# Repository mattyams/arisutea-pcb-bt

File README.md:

# VERY MUCH ALPHA BLUETOOTH VERSION!
# THIS IS STILL A WIP! NO GUARANTEES ON ANYTHING!
# Arisutea - Arisu Bluetooth Keyboard PCB
## Disclaimer: Use these files at your own risk.
アリステア PCB designed using KiCad. The layout was originally created by FateNozomi, inspired by Lyn's EM7 and TGR Alice with some modification. The layout was then modified by CorruptedJef and robotictomato to add Bluetooth using a Holyiot 18010, USB-C, ESD and to shift/add some keys. This inspired me to modify the layout further by adding the ability to swap your switches out whenever you want and to make some keys a little more permenant. I have designed many boards in the past but never a keyboard so this is my first crack at it and I figured why not go all out? If you notice any issue please open an issue and we can discuss!

Since the layout has been modified yet again I decided to give the project a new name, Arisutea, which translates to Alistair. Obviously keeping the theme running here. 

Key modifications to the PCB:
- Bluetooth using a Holyiot 18010.
- Added in Kailh Hotswap sockets.
- Addition of full backspace position, connected to switch 59 (row 0, column 13).
  - Removed switch 63 and repositioned switch 59 to add full backspace position.
- USB-C ESD rework.
- Added LED indicators for CAPS and NUM lock as well as layer.
- Updated JSON layout file for this particular keyboard.
- Original mounting holes have been widened to allow for M2+ standoffs to pass through the PCB to the FR4 plates linked below, so if you planned on using this in a different case other than the one provided or these plates....you might have a bad time. 

# ZMK Firmware
I plan to use ZMK for this board once I get it finalized.

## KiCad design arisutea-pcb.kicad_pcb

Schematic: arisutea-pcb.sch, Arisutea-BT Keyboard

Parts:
BT1: Battery_Cell; Battery_Connector
BT2: Battery_Cell; JST_PH_S2B-PH-K_1x02_P2.00mm_Horizontal
C1: 4.7uF; C_0805_2012Metric_Pad1.18x1.45mm_HandSolder
C2, C3: 1uF; C_0805_2012Metric_Pad1.18x1.45mm_HandSolder
D1: 1N5819; D_SOD-123
F1: 500mA; Fuse_1206_3216Metric_Pad1.42x1.75mm_HandSolder
H1, H2, H3, H4, H5, H6, H7, H8: ThroughHole; Generic-Mounthole
J1: Conn_01x04; PinHeader_1x04_P2.54mm_Vertical
LED1: PWR_LED; LED_IN-S124ARUW
LED2: NUM_LOCK; LED_IN-S124ARUW
LED3: CAPS_LOCK; LED_IN-S124ARUW
LED4: FN_LED; LED_IN-S124ARUW
LED5: BAT_LED; LED_IN-S124ARUW
LOGO1, LOGO2: arisutea_logo
Q1: AO3401A; SOT-23
R1, R2: 5k1; R_0805_2012Metric_Pad1.20x1.40mm_HandSolder; LCSC C27834
R3, R4: 22; R_0805_2012Metric_Pad1.20x1.40mm_HandSolder; LCSC C17561
R5: 806K; R_0805_2012Metric_Pad1.20x1.40mm_HandSolder; LCSC C17561
R6: 2M; R_0805_2012Metric_Pad1.20x1.40mm_HandSolder; LCSC C17561
R7: 10K; R_0805_2012Metric_Pad1.20x1.40mm_HandSolder; LCSC C17561
R8: 1k; R_0805_2012Metric_Pad1.20x1.40mm_HandSolder; LCSC C17561
R9: 10K; R_0805_2012Metric_Pad1.20x1.40mm_HandSolder; LCSC C17414
R10: 1K; R_0805_2012Metric_Pad1.20x1.40mm_HandSolder; LCSC C17561
R11, R12, R13: 470; R_0805_2012Metric_Pad1.20x1.40mm_HandSolder
SW67: Switch; OS102011MA1QN1
SWR1: SW_Push; SW_SPST_TL3342; LCSC C318884
U1: nRF52840_holyiot_18010; nRF52840_holyiot_18010_HS_simple
U2: USBLC6-2SC6; SOT-23-6_Handsoldering; LCSC C7519
U3: TP4504; SOT-23-5
U4: AP2112K-3.3; SOT-23-5
USB1: HRO-TYPE-C-31-M-12-Type-C; USB_C_Receptacle_HRO_TYPE-C-31-M-12-HandSoldering

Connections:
CAPS_L: R12.2, U1.16
D+: R4.1, U1.24
D-: R3.1, U1.23
FN_L: R11.2, U1.17
GND: BT1.2, BT2.2, C1.1, C2.2, C3.2, J1.3, LED2.C, LED3.C, LED4.C, R1.1, R2.1, R6.1, R7.2, R9.2, R10.1, SWR1.1 (COL), U1.1, U1.25, U1.37, U2.2, U3.2, U4.2, USB1.1, USB1.12, USB1.13
NUM_L: R13.2, U1.15
unnamed: BT1.1, BT2.1, SW67.1 (COL)
unnamed: C3.1, D1.1, Q1.2, U4.1, U4.3
unnamed: LED1.A, R8.2
unnamed: LED1.C, U3.1
unnamed: LED2.A, R11.1
unnamed: LED3.A, R12.1
unnamed: LED4.A, R13.1
unnamed: LED5.C, R10.2
unnamed: R1.2, USB1.4
unnamed: R2.2, USB1.10
unnamed: R3.2, U2.6
unnamed: R4.2, U2.4
unnamed: R7.1, U3.5
unnamed: U2.1, USB1.5, USB1.7
unnamed: U2.3, USB1.6, USB1.8
VBUS: D1.2, F1.2, J1.4, Q1.1, R8.1, R9.1, U1.22, U3.4
VDD_nRF: C2.1, U1.14, U4.5
bat_led: LED5.A, U1.18
bat_volt: R5.1, R6.2, U1.12
col6: U1.33; also elsewhere on the board
col7: U1.34; also elsewhere on the board
col8: U1.35; also elsewhere on the board
col9: U1.36; also elsewhere on the board
col10: U1.30; also elsewhere on the board
col11: U1.29; also elsewhere on the board
col12: U1.28; also elsewhere on the board
col13: U1.27; also elsewhere on the board
col14: U1.26; also elsewhere on the board
reset: SWR1.2 (ROW), U1.21
row0: U1.11; also elsewhere on the board
row1: U1.10; also elsewhere on the board
row2: U1.5; also elsewhere on the board
row3: U1.3; also elsewhere on the board
row4: U1.4; also elsewhere on the board
swdclk: J1.2, U1.31
swdio: J1.1, U1.32
vbat: C1.2, Q1.3, R5.2, SW67.2 (ROW), U3.3
vbus_usb: F1.1, U2.5, USB1.2, USB1.11

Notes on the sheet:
USB Connection, ESD & Fuse
Battery Management
Voltage Reg & Reset Switch

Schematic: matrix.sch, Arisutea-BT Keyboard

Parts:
D2, D3, D4, D5, D6, D7, D8, D9, D10, D11, D12, D13, D14, D15, D16, D17, D18, D19, D20, D21, D22, D23, D24, D25, D26, D27, D28, D29, D30, D31, D32, D33, D34, D35, D36, D37, D38, D39, D40, D41, D42, D43, D44, D45, D46, D47, D48, D49, D50, D51, D52, D53, D54, D55, D56, D57, D58, D59, D60, D61, D62, D63, D64, D65, D66, D67: D; D_SOD-123; LCSC C81598
SW1, SW2, SW3, SW4, SW5, SW6, SW7, SW8, SW9, SW10, SW11, SW12, SW13, SW16, SW17, SW18, SW19, SW20, SW21, SW22, SW23, SW24, SW25, SW26, SW27, SW29, SW31, SW32, SW33, SW34, SW35, SW36, SW37, SW38, SW39, SW40, SW41, SW43, SW45, SW46, SW47, SW48, SW49, SW50, SW51, SW52, SW53, SW54, SW56, SW57, SW59, SW61, SW63, SW64, SW65, SW66: SW_Push; SW_Hotswap_Kailh_1.00u
SW14: SW_Push; SW_Hotswap_Kailh_2.00u
SW15, SW28, SW58: SW_Push; SW_Hotswap_Kailh_1.50u
SW30, SW55: SW_Push; SW_Hotswap_Kailh_1.75u
SW42: SW_Push; SW_Hotswap_Kailh_2.25u_RevStab
SW44: SW_Push; SW_Hotswap_Kailh_2.25u
SW60: SW_Push; SW_Hotswap_Kailh_2.00u_RevStab
SW62: SW_Push; SW_Hotswap_Kailh_2.75u_RevStab

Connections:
unnamed: D2.2 (A), SW1.2
unnamed: D3.2 (A), SW2.2
unnamed: D4.2 (A), SW3.2
unnamed: D5.2 (A), SW4.2
unnamed: D6.2 (A), SW5.2
unnamed: D7.2 (A), SW6.2
unnamed: D8.2 (A), SW7.2
unnamed: D9.2 (A), SW8.2
unnamed: D10.2 (A), SW9.2
unnamed: D11.2 (A), SW10.2
unnamed: D12.2 (A), SW11.2
unnamed: D13.2 (A), SW12.2
unnamed: D14.2 (A), SW13.2
unnamed: D15.2 (A), SW14.2
unnamed: D16.2 (A), SW15.2
unnamed: D17.2 (A), SW16.2
unnamed: D18.2 (A), SW17.2
unnamed: D19.2 (A), SW18.2
unnamed: D20.2 (A), SW19.2
unnamed: D21.2 (A), SW20.2
unnamed: D22.2 (A), SW21.2
unnamed: D23.2 (A), SW22.2
unnamed: D24.2 (A), SW23.2
unnamed: D25.2 (A), SW24.2
unnamed: D26.2 (A), SW25.2
unnamed: D27.2 (A), SW26.2
unnamed: D28.2 (A), SW27.2
unnamed: D29.2 (A), SW28.2
unnamed: D30.2 (A), SW29.2
unnamed: D31.2 (A), SW30.2
unnamed: D32.2 (A), SW31.2
unnamed: D33.2 (A), SW32.2
unnamed: D34.2 (A), SW33.2
unnamed: D35.2 (A), SW34.2
unnamed: D36.2 (A), SW35.2
unnamed: D37.2 (A), SW36.2
unnamed: D38.2 (A), SW37.2
unnamed: D39.2 (A), SW38.2
unnamed: D40.2 (A), SW39.2
unnamed: D41.2 (A), SW40.2
unnamed: D42.2 (A), SW41.2
unnamed: D43.2 (A), SW42.2
unnamed: D44.2 (A), SW43.2
unnamed: D45.2 (A), SW44.2
unnamed: D46.2 (A), SW45.2
unnamed: D47.2 (A), SW46.2
unnamed: D48.2 (A), SW47.2
unnamed: D49.2 (A), SW48.2
unnamed: D50.2 (A), SW49.2
unnamed: D51.2 (A), SW50.2
unnamed: D52.2 (A), SW51.2
unnamed: D53.2 (A), SW52.2
unnamed: D54.2 (A), SW53.2
unnamed: D55.2 (A), SW54.2
unnamed: D56.2 (A), SW55.2
unnamed: D57.2 (A), SW56.2
unnamed: D58.2 (A), SW57.2
unnamed: D59.2 (A), SW58.2
unnamed: D60.2 (A), SW59.2
unnamed: D61.2 (A), SW60.2
unnamed: D62.2 (A), SW61.2
unnamed: D63.2 (A), SW62.2
unnamed: D64.2 (A), SW63.2
unnamed: D65.2 (A), SW64.2
unnamed: D66.2 (A), SW65.2
unnamed: D67.2 (A), SW66.2
col0: SW1.1, SW15.1, SW30.1, SW44.1, SW58.1
col1: SW2.1, SW16.1, SW31.1, SW45.1
col2: SW3.1, SW17.1, SW32.1, SW46.1, SW59.1
col3: SW4.1, SW18.1, SW33.1, SW47.1
col4: SW5.1, SW19.1, SW34.1, SW48.1, SW60.1
col5: SW6.1, SW20.1, SW35.1, SW49.1, SW61.1
col6: SW7.1, SW21.1, SW36.1, SW50.1; also elsewhere on the board
col7: SW8.1, SW22.1, SW37.1, SW51.1, SW62.1; also elsewhere on the board
col8: SW9.1, SW23.1, SW38.1, SW52.1; also elsewhere on the board
col9: SW10.1, SW24.1, SW39.1, SW53.1, SW63.1; also elsewhere on the board
col10: SW11.1, SW25.1, SW40.1, SW54.1; also elsewhere on the board
col11: SW12.1, SW26.1, SW41.1, SW55.1; also elsewhere on the board
col12: SW13.1, SW27.1, SW42.1, SW64.1; also elsewhere on the board
col13: SW14.1, SW28.1, SW56.1, SW65.1; also elsewhere on the board
col14: SW29.1, SW43.1, SW57.1, SW66.1; also elsewhere on the board
row0: D2.1 (K), D3.1 (K), D4.1 (K), D5.1 (K), D6.1 (K), D7.1 (K), D8.1 (K), D9.1 (K), D10.1 (K), D11.1 (K), D12.1 (K), D13.1 (K), D14.1 (K), D15.1 (K); also elsewhere on the board
row1: D16.1 (K), D17.1 (K), D18.1 (K), D19.1 (K), D20.1 (K), D21.1 (K), D22.1 (K), D23.1 (K), D24.1 (K), D25.1 (K), D26.1 (K), D27.1 (K), D28.1 (K), D29.1 (K), D30.1 (K); also elsewhere on the board
row2: D31.1 (K), D32.1 (K), D33.1 (K), D34.1 (K), D35.1 (K), D36.1 (K), D37.1 (K), D38.1 (K), D39.1 (K), D40.1 (K), D41.1 (K), D42.1 (K), D43.1 (K), D44.1 (K); also elsewhere on the board
row3: D45.1 (K), D46.1 (K), D47.1 (K), D48.1 (K), D49.1 (K), D50.1 (K), D51.1 (K), D52.1 (K), D53.1 (K), D54.1 (K), D55.1 (K), D56.1 (K), D57.1 (K), D58.1 (K); also elsewhere on the board
row4: D59.1 (K), D60.1 (K), D61.1 (K), D62.1 (K), D63.1 (K), D64.1 (K), D65.1 (K), D66.1 (K), D67.1 (K); also elsewhere on the board

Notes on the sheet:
ESC
TAB
ENT
RGHT
LEFT
DOWN
SPC
ALT
CTRL
SHFT
SHIFT
CAPS
BKSP

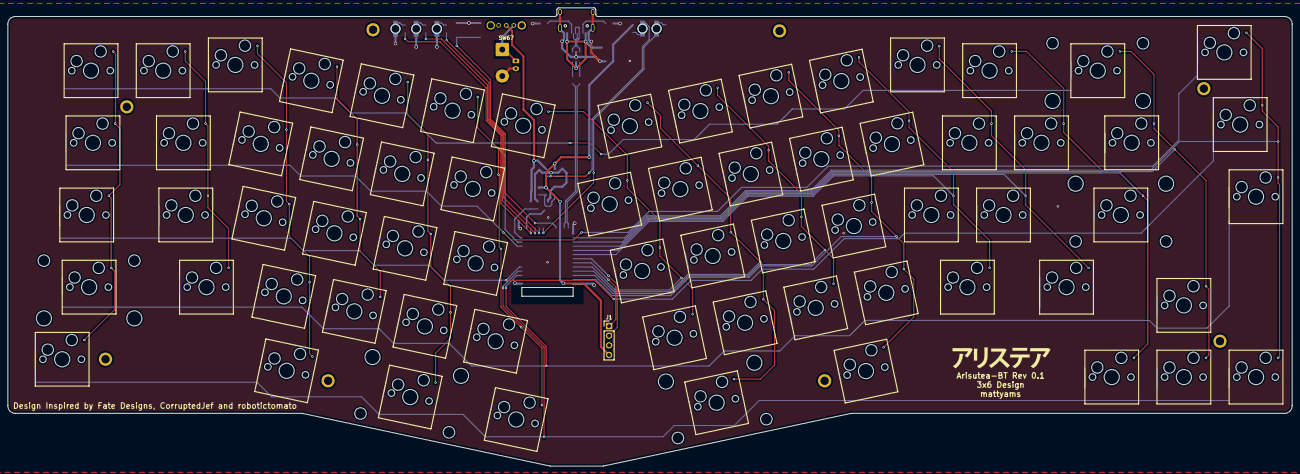
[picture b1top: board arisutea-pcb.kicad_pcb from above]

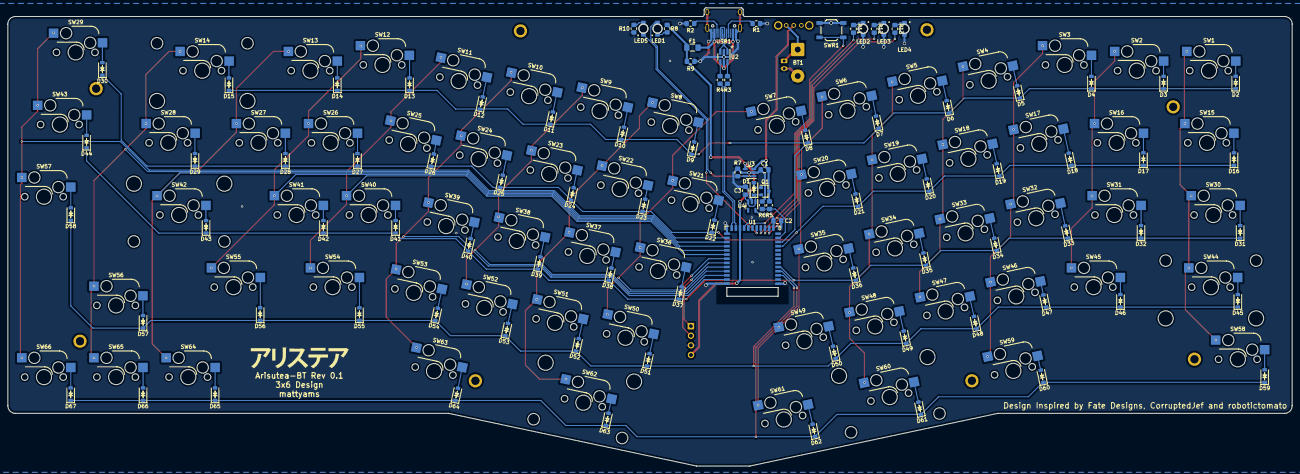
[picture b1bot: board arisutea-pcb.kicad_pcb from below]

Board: 2 copper layers, 339.1 x 121.0 mm, 176 parts (99 on the bottom side), 116 nets.

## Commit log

2021-04-04 correction to boxed case back plate
2021-04-10 housecleaning
2021-04-13 underglow header placement moved a bit, add logos, move some components
2021-04-25 ibom and case revisions
2021-04-27 Initial upload of bluetooth version
